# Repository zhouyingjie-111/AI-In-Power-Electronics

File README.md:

# AI+电力电子智能设计系统 🚀

<div align="center">

**从指标到硬件AI+电力电子设计系统**

[功能特性](#-功能特性) • [快速开始](#-快速开始) • [使用指南](#-使用指南) • [技术栈](#-技术栈) • [贡献指南](#-贡献指南) 

</div>

---

## 📖 项目简介

AI+电力电子智能设计平台是一个集成了人工智能算法、电力电子仿真和自动化设计的综合性Web应用平台。该平台致力于通过AI技术优化Buck变换器等电力电子设备的设计流程，实现从参数优化、仿真验证到PCB设计的全自动化工作流。

### 🎯 核心价值

- **智能优化**：采用PPO强化学习算法自动优化电路参数，提升设计效率
- **仿真验证**：集成MATLAB/Simulink环境，实时验证设计性能
- **自动化设计**：从原理图到PCB布局的自动生成与优化
- **智能交互**：基于大语言模型的技术咨询与问题解答
- **远程协作**：支持公网访问和远程桌面控制，便于团队协作

### 🌟 应用场景

- 电力电子工程师的参数设计与优化
- 教学科研中的电路仿真与实验
- 企业级电力电子产品开发
- 自动化PCB设计与制造

---

## ✨ 功能特性

### 1. 🎛️ 参数智能设计

- 基于**PPO（Proximal Policy Optimization）强化学习算法**自动优化Buck变换器参数
- 支持多目标优化：效率、纹波、动态响应等
- 实时显示训练进度和性能曲线
- 自动保存最优参数配置

### 2. 🔬 仿真验证

- 无缝集成**MATLAB/Simulink**仿真环境
- 支持自定义参数仿真和优化参数验证
- 实时流式输出仿真日志
- 自动生成性能分析报告和波形图

### 3. 🔌 原理图/PCB自动设计

- 基于设计参数自动生成原理图
- 智能器件选型与推荐
- PCB布局布线初步方案生成
- 集成KiCad等EDA工具支持

### 4. 💻 控制器代码生成

- 自动生成嵌入式控制器代码模板
- 支持多种微控制器平台（STM32、TI DSP等）
- Simulink控制逻辑自动转换
- 代码优化与注释生成

### 5. 💬 智能对话助手

- 集成大语言模型提供技术咨询
- 电力电子专业知识问答
- 设计建议与故障诊断
- 实时对话交互

### 6. 🗄️ 数据库管理

- 可视化数据库操作界面
- 支持CSV文件导入导出
- 历史设计方案管理
- 数据备份与恢复

### 7. 🖥️ 远程桌面控制

- 支持远程鼠标键盘操作
- 实时屏幕共享
- 窗口管理与应用控制
- 密码保护与安全访问

### 8. 🌐 公网访问支持

- 支持固定域名访问
- HTTPS安全传输
- 多人同时在线协作

---

## 🚀 快速开始

### 环境要求

- **Python**: 3.8 或更高版本
- **MATLAB**: R2018b 或更高版本（需要MATLAB Engine API for Python）
- **操作系统**: Windows 10/11（支持部分远程控制功能）

### 安装步骤

#### 1. 克隆项目

```bash
git clone <repository-url>
cd "AI-based optimized design/Code/python/webapp"
```

#### 2. 安装Python依赖

```bash
pip install -r requirements.txt
```

**主要依赖包：**

```
flask>=2.0.0
waitress>=2.1.0
mss>=6.1.0
pillow>=9.0.0
pywin32>=300
openai>=1.0.0
psutil>=5.9.0
pandas>=1.3.0
pyngrok>=5.1.0
```

#### 3. 安装MATLAB Engine（可选，用于仿真功能）

```bash
# 进入MATLAB安装目录
cd "matlabroot\extern\engines\python"
python setup.py install
```

> **注意**: 将`matlabroot`替换为实际的MATLAB安装路径，例如：`C:\Program Files\MATLAB\R2024b`

#### 4. 配置环境变量（可选）

创建`.env`文件或设置系统环境变量：

```bash
# Flask配置
WEBAPP_SECRET_KEY=your-secret-key-here

# 服务器配置
HOST=0.0.0.0
PORT=5000

# Ngrok配置（公网访问）
NGROK_AUTHTOKEN=your-ngrok-token
NGROK_REGION=us  # 或 eu, ap, au, sa, jp, in

# OpenAI API（智能对话功能）
OPENAI_API_KEY=your-openai-api-key
```

#### 5. 配置密码

编辑`roles_passwords.json`设置管理员和用户密码：

```json
{
  "admin": "your-admin-password",
  "user": "your-user-password"
}
```

#### 6. 启动应用

```bash
python app.py
```

启动成功后，控制台会显示访问地址：

```
[startup] AI+电力电子 已启动 (生产服务器: waitress)
[startup] 本机访问:    http://127.0.0.1:5000
[startup] 局域网访问:  http://x.x.x.x:5000
[startup] 公网访问:    https://ai_power_electronics.aipowerelectronics.top
```

---

## 📚 使用指南

### 基本工作流程

```mermaid
graph LR
    A[登录系统] --> B[选择角色]
    B --> C[主界面]
    C --> D[参数设计]
    C --> E[仿真验证]
    C --> F[原理图/PCB自动设计]
    C --> G[控制器代码自动生成]
    C --> H[智能对话]
    D --> J[硬件选型]
    D --> E
    E --> F
    F --> G
    G --> H
    I[数据库维护]
```

### 1. 参数设计流程

**步骤：**

1. 在主界面点击 **"参数设计"** 卡片
2. 系统启动PPO训练算法
3. 实时查看训练进度和性能曲线
4. 等待训练完成，系统自动保存最优参数
5. 查看优化结果和性能指标

### 2. 仿真验证流程

**步骤：**

1. 点击 **"仿真验证"** 按钮
2. 选择仿真模式：
   - **优化参数仿真**：使用PPO优化的参数
   - **自定义参数仿真**：手动输入参数
3. 查看实时仿真日志
4. 等待仿真完成，下载结果报告

### 3. 原理图/PCB设计

**步骤：**

1. 点击 **"原理图/PCB自动设计"**
2. 系统根据优化参数自动选型
3. 生成原理图和PCB初稿
4. 支持手动调整和优化
5. 导出KiCad工程文件

### 4. 智能对话

**使用方式：**

- 点击 **"智能对话"** 进入AI助手界面
- 输入问题或需求，获取专业建议
- 支持多轮对话和上下文理解

### 5. 数据库管理

**功能：**

- **查看数据**：浏览历史设计方案
- **导入数据**：上传CSV文件
- **导出数据**：下载设计结果
- **数据备份**：定期备份重要数据

---

## 🛠️ 技术栈

### 后端技术

| 技术 | 版本 | 用途 |
|------|------|------|
| **Python** | 3.8+ | 核心开发语言 |
| **Flask** | 2.0+ | Web框架 |
| **Waitress** | 2.1+ | WSGI生产服务器 |
| **MATLAB Engine** | R2024b+ | 仿真引擎接口 |

### 前端技术

| 技术 | 用途 |
|------|------|
| **HTML5/CSS3** | 页面结构与样式 |
| **JavaScript (ES6+)** | 交互逻辑 |
| **Server-Sent Events** | 实时日志流 |
| **Canvas API** | 远程桌面渲染 |

### 核心算法

- **PPO (Proximal Policy Optimization)**: 强化学习参数优化
- **Multi-Task ResNet**: 神经网络模型（MT-ResNet）

### 支持工具

| 工具 | 用途 |
|------|------|
| **Ngrok** | 公网穿透 |
| **mss** | 屏幕截图 |
| **pywin32** | Windows API调用 |
| **PIL/Pillow** | 图像处理 |
| **psutil** | 进程管理 |
| **pandas** | 数据处理 |

### 系统架构

```
┌─────────────────────────────────────────────────┐
│                   用户界面层                     │
│  (HTML/CSS/JavaScript + SSE实时通信)            │
└─────────────────┬───────────────────────────────┘
                  │
┌─────────────────┴───────────────────────────────┐
│                Flask应用层                       │
│  • 路由管理 • 会话控制 • API接口                  │
└─────────────────┬───────────────────────────────┘
                  │
        ┌─────────┴─────────┐
        │                   │
┌───────┴────────┐  ┌───────┴──────┐
│  业务逻辑层     │  │   数据访问层  │
│  • PPO训练     │  │  • CSV读写    │
│  • 仿真控制     │  │  • 模型加载   │
│  • EDA自动化    │  │  • 数据管理   │
└───────┬────────┘  └───────┬───────┘
        │                   │
┌───────┴───────────────────┴────────┐
│            外部接口层               │
│  • MATLAB Engine                   │
│  • Ngrok                           │
│  • Windows API                     │
└────────────────────────────────────┘
```

---

## 🎨 界面预览

### 主界面

主界面采用卡片式设计，清晰展示各功能模块：

- **渐变色标题**：现代化视觉效果
- **悬停动画**：流畅的交互体验
- **响应式布局**：适配各种屏幕尺寸
- **状态栏**：实时显示系统状态

### 运行界面

- **实时日志流**：Server-Sent Events推送
- **进度条**：可视化任务进度
- **停止控制**：随时中断任务
- **结果展示**：自动显示输出文件

---

## 🔧 配置说明

### 1. 密码配置

**`roles_passwords.json`**: 角色密码配置

```json
{
  "admin": "管理员密码",
  "user": "普通用户密码"
}
```

### 2. 远程控制密码

**`remote_mouse_password.txt`**: 远程鼠标控制密码

```
your_password
```

### 3. Ngrok配置

设置环境变量启用公网访问：

```bash
export NGROK_AUTHTOKEN=your_token_here
export NGROK_REGION=us  # 可选: us, eu, ap, au, sa, jp, in
```

## 🤝 贡献指南

我们欢迎所有形式的贡献！无论是新功能、Bug修复、文档改进还是问题反馈。

### 贡献流程

1. **Fork项目**

```bash
git clone https://github.com/your-username/AI-based-optimized-design.git
cd AI-based-optimized-design
```

2. **创建特性分支**

```bash
git checkout -b feature/your-feature-name
```

3. **提交更改**

```bash
git add .
git commit -m "feat: 添加新功能描述"
```

4. **推送到远程**

```bash
git push origin feature/your-feature-name
```

5. **创建Pull Request**

在GitHub上创建PR，详细描述您的更改。

## 📄 License

详见 [LICENSE]文件。

**⭐ 如果这个项目对您有帮助，请给我们一个Star！⭐**

南航电力电子团队

</div>

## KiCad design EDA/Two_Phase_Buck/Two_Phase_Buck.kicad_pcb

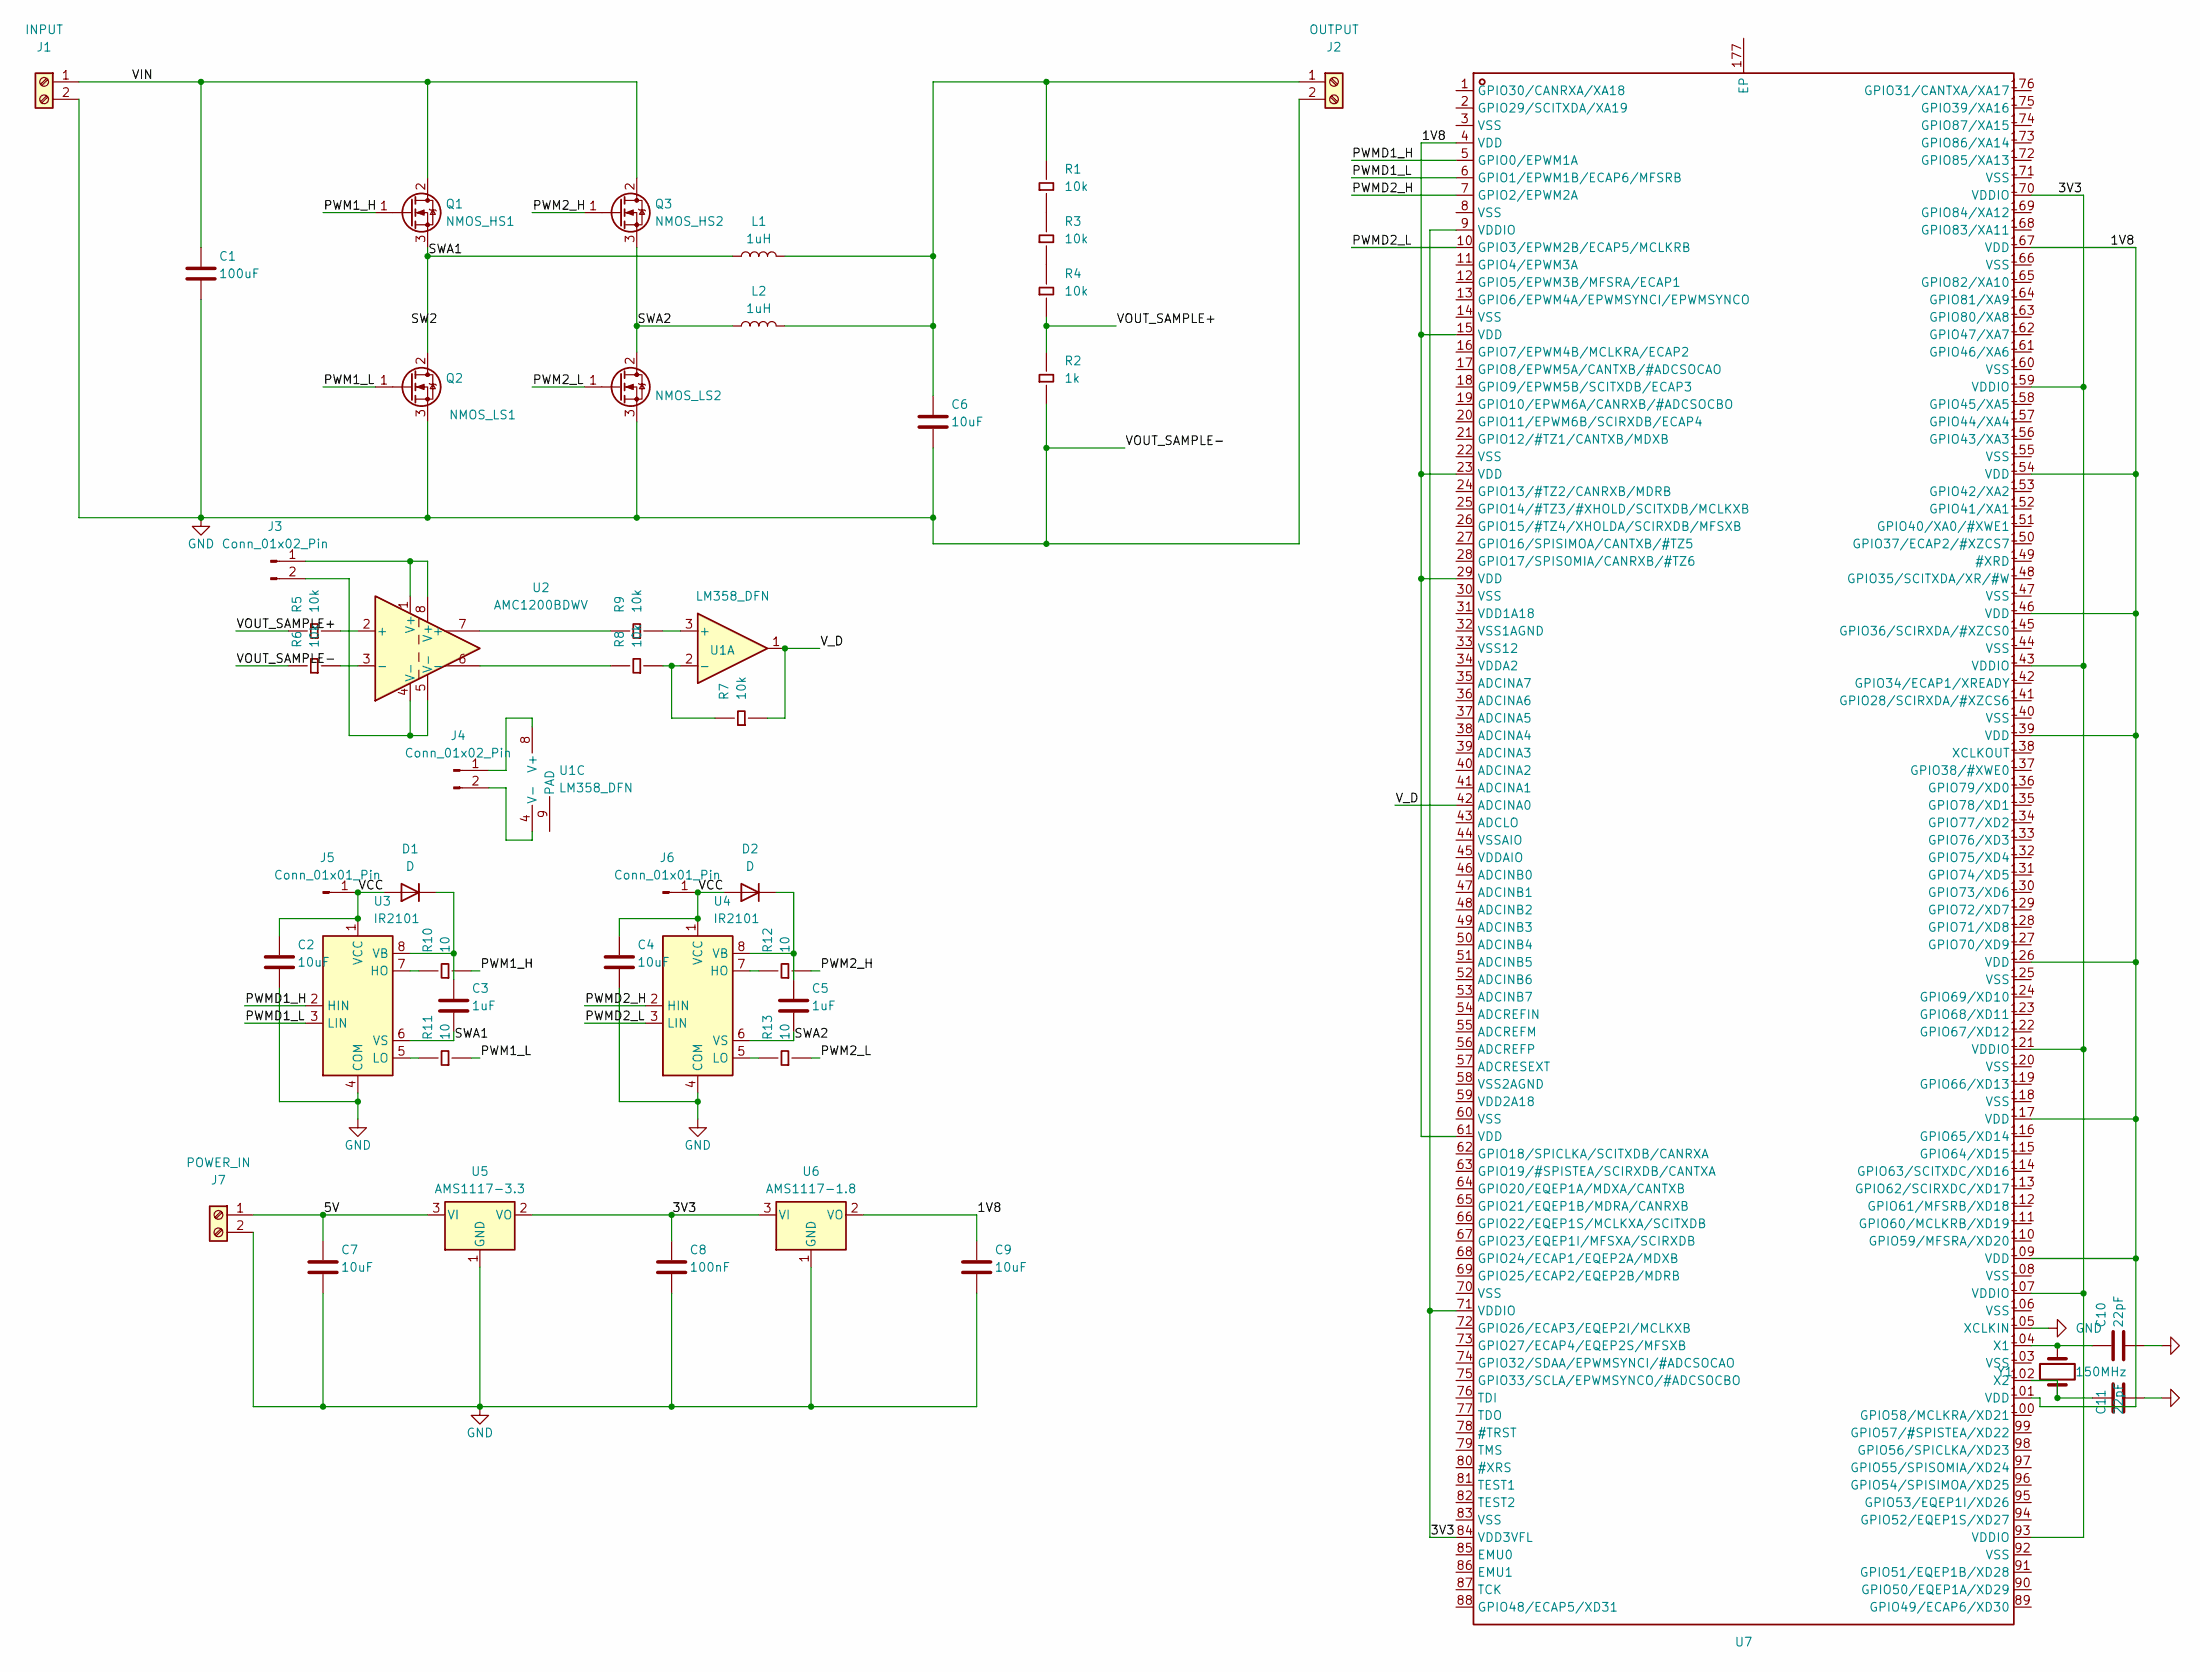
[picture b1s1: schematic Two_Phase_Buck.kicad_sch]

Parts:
C1: 100uF; C_1206_3216Metric
C2, C4, C6: 10uF; C_1206_3216Metric
C3, C5: 1uF; C_1206_3216Metric
C7, C9: 10uF; C_0805_2012Metric
C8: 100nF; C_0603_1608Metric
C10, C11: 22pF; C_0603_1608Metric
D1, D2: D; D_0603_1608Metric
J1: INPUT; TerminalBlock_bornier-2_P5.08mm
J2: OUTPUT; TerminalBlock_bornier-2_P5.08mm
J3, J4: Conn_01x02_Pin; PinHeader_1x02_P1.00mm_Vertical
J5, J6: Conn_01x01_Pin; PinHeader_1x01_P2.54mm_Vertical
J7: POWER_IN; TerminalBlock_bornier-2_P5.08mm
L1, L2: 1uH; L_12x12mm_H8mm
Q1: NMOS_HS1; TO-252-2
Q2: NMOS_LS1; TO-252-2
Q3: NMOS_HS2; TO-252-2
Q4: NMOS_LS2; TO-252-2
R1, R3, R4, R5, R6, R7, R8, R9: 10k; R_0603_1608Metric
R2: 1k; R_0603_1608Metric
R10, R11, R12, R13: 10; R_0603_1608Metric
U1: LM358_DFN; DFN-8-1EP_2x2mm_P0.5mm_EP1.05x1.75mm
U2: AMC1200BDWV; SOIC-8_7.5x5.85mm_P1.27mm
U3, U4: IR2101; TSSOP-8_3x3mm_P0.65mm
U5: AMS1117-3.3; SOT-223-3_TabPin2
U6: AMS1117-1.8; SOT-223-3_TabPin2
U7: TMS320F28335PTPQ; DSP28335; Voltage - Supply 1.805V~1.995V; Manufacturer Part TMS320F28335PTPQ; LCSC Part Name 具有 150MIPS、FPU、512KB 闪存、EMIF、12 位 ADC 的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
Y1: 150MHz; Crystal_SMD_HC49-SD

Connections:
/1V8: C9.1, U6.2 (VO), U7.4 (VDD), U7.15 (VDD), U7.23 (VDD), U7.29 (VDD), U7.61 (VDD), U7.101 (VDD), U7.109 (VDD), U7.117 (VDD), U7.126 (VDD), U7.139 (VDD), U7.146 (VDD), U7.154 (VDD), U7.167 (VDD)
/3V3: C8.1, U5.2 (VO), U6.3 (VI), U7.9 (VDDIO), U7.71 (VDDIO), U7.84 (VDD3VFL), U7.93 (VDDIO), U7.107 (VDDIO), U7.121 (VDDIO), U7.143 (VDDIO), U7.159 (VDDIO), U7.170 (VDDIO)
/5V: C7.1, J7.1, U5.3 (VI)
/PWM1_H: Q1.1 (G), R10.2
/PWM1_L: Q2.1 (G), R11.2
/PWM2_H: Q3.1 (G), R12.2
/PWM2_L: Q4.1 (G), R13.2
/PWMD1_H: U3.2 (HIN), U7.5 (GPIO0/EPWM1A)
/PWMD1_L: U3.3 (LIN), U7.6 (GPIO1/EPWM1B/ECAP6/MFSRB)
/PWMD2_H: U4.2 (HIN), U7.7 (GPIO2/EPWM2A)
/PWMD2_L: U4.3 (LIN), U7.10 (GPIO3/EPWM2B/ECAP5/MCLKRB)
/SWA1: C3.2, L1.1, Q1.3 (S), Q2.2 (D), U3.6 (VS)
/SWA2: C5.2, L2.1, Q3.3 (S), Q4.2 (D), U4.6 (VS)
/VCC: C2.1, C4.1, D1.2 (A), D2.2 (A), J5.1, J6.1, U3.1 (VCC), U4.1 (VCC)
/VIN: C1.1, J1.1, Q1.2 (D), Q3.2 (D)
/VOUT_SAMPLE+: R2.1, R4.2, R5.1
/V_D: R7.2, U1.1, U7.42 (ADCINA0)
GND: C1.2, C2.2, C4.2, C6.2, C7.2, C8.2, C9.2, C10.2, C11.2, J1.2, J2.2, J7.2, Q2.3 (S), Q4.3 (S), R2.2, R6.1, U3.4 (COM), U4.4 (COM), U5.1 (GND), U6.1 (GND), U7.105 (XCLKIN)
unnamed: C3.1, D1.1 (K), U3.8 (VB)
unnamed: C5.1, D2.1 (K), U4.8 (VB)
unnamed: C6.1, J2.1, L1.2, L2.2, R1.1
unnamed: J3.1, U2.1 (V+), U2.8 (V+)
unnamed: J3.2, U2.4 (V-), U2.5 (V-)
unnamed: J4.1, U1.8 (V+)
unnamed: J4.2, U1.4 (V-)
unnamed: R1.2, R3.1
unnamed: R3.2, R4.1
unnamed: R5.2, U2.2 (+)
unnamed: R6.2, U2.3 (-)
unnamed: R8.1, U2.6 (-)
unnamed: R9.1, U2.7 (+)
unnamed: R9.2, U1.3 (+)
unnamed: R7.1, R8.2, U1.2 (-)
unnamed: R10.1, U3.7 (HO)
unnamed: R11.1, U3.5 (LO)
unnamed: R12.1, U4.7 (HO)
unnamed: R13.1, U4.5 (LO)
unnamed: C10.1, U7.104 (X1), Y1.2
unnamed: C11.1, U7.102 (X2), Y1.1

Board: 2 copper layers, 47 parts (0 on the bottom side), 39 nets, no tracks yet.

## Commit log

2025-11-04 Enhance README with project details and guidelines
    Added detailed project description, features, usage guidelines, and contribution instructions to README.
2025-11-04 Fix formatting and remove heart emoji from README
2025-11-04 Update project title and description in README

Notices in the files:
README.md:
License: MIT
